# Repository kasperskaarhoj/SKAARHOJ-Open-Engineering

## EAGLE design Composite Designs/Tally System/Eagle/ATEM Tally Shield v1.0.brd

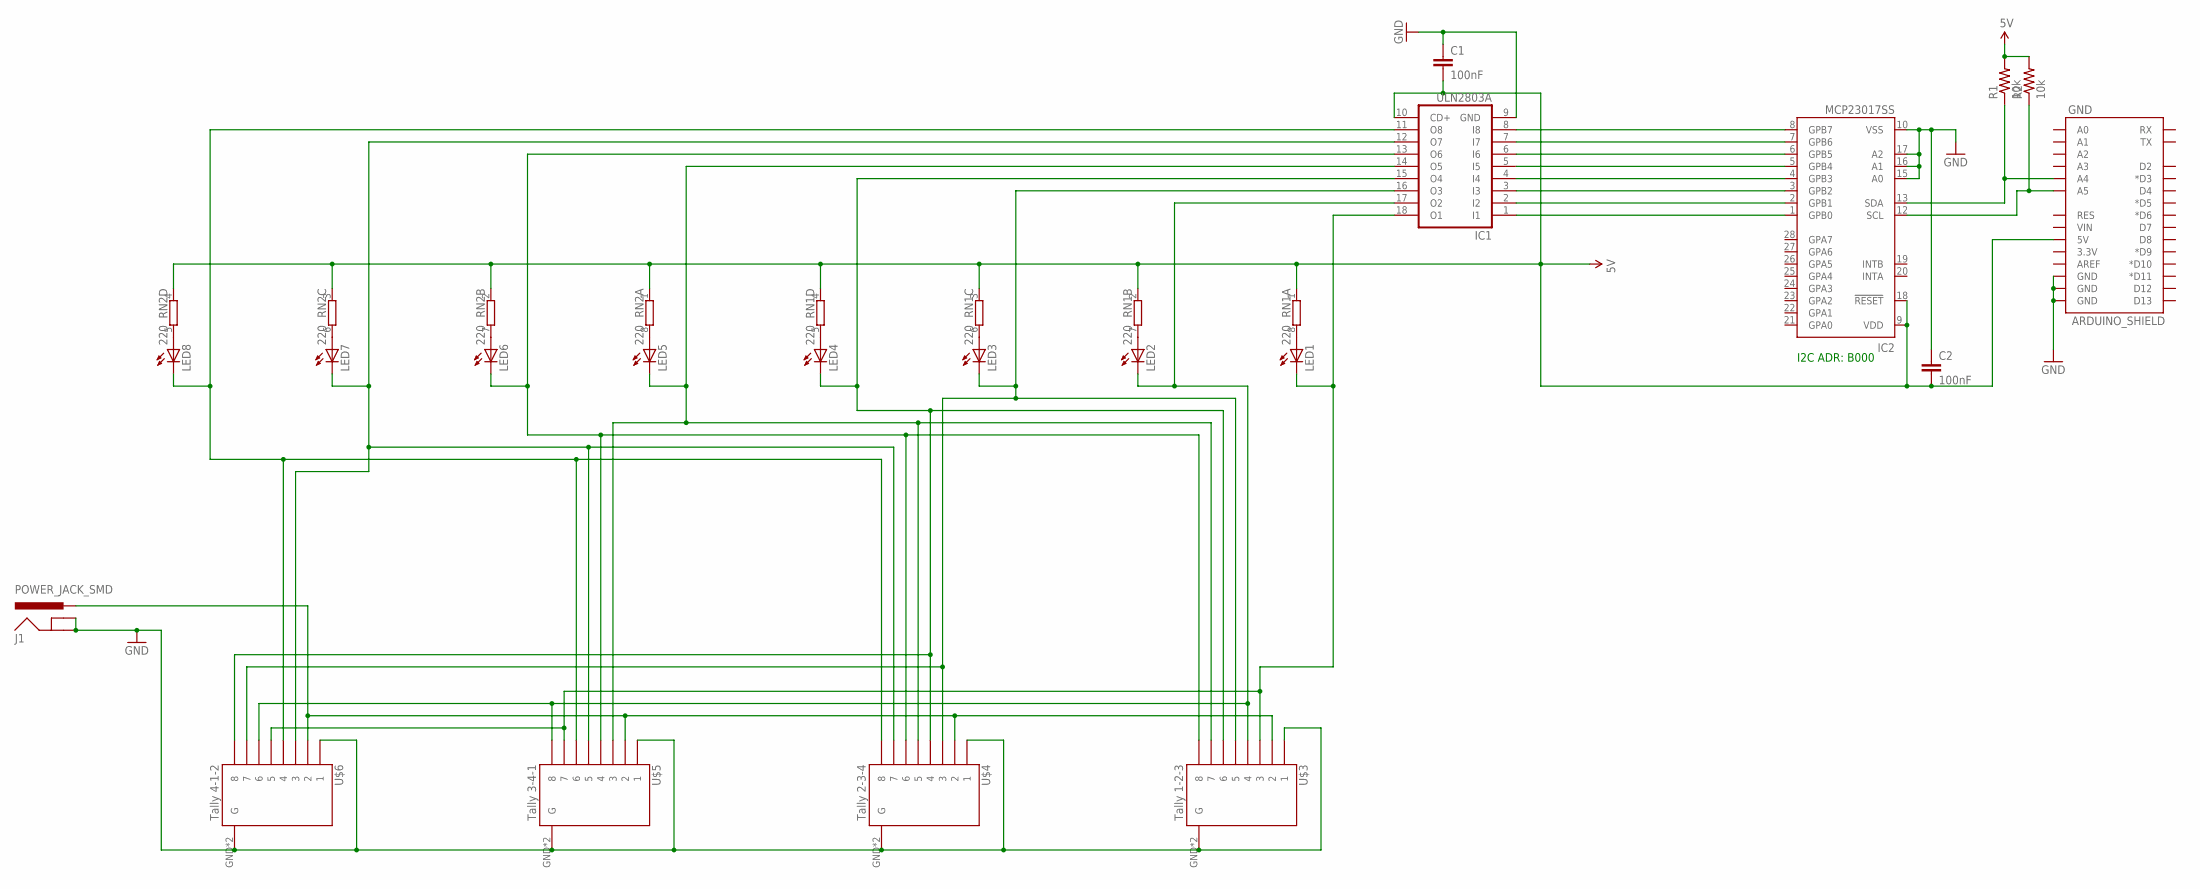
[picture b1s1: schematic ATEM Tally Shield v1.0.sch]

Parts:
C1: 100nF; 0805
C2: 100nF; 0603-CAP
GND: ARDUINO_SHIELD; ARDUINO_BOXSHIELD_NOHOLES
IC1: ULN2803A; SO18W
IC2: MCP23017SS; SSOP28
J1: POWER_JACK_SMD
LED1, LED2, LED3, LED4, LED5, LED6, LED7, LED8: LEDSML0805; SML0805
R1, R2: 10k; 0603-RES
RN1, RN2: 220; CAY16_HAND
U$3: Tally 1-2-3; RJ45-8_GND
U$4: Tally 2-3-4; RJ45-8_GND
U$5: Tally 3-4-1; RJ45-8_GND
U$6: Tally 4-1-2; RJ45-8_GND

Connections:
5V: C1.2, C2.2, GND.5V@0 (5V), IC1.10 (CD+), IC2.9 (VDD), IC2.18 (!RESET), R1.2, R2.2, RN1.1, RN1.2 (1), RN1.3 (1), RN1.4 (1), RN2.1, RN2.2 (1), RN2.3 (1), RN2.4 (1)
GND: C1.1, C2.1, GND.GND@0 (GND), GND.GND@1 (GND), GND.GND@4 (GND), IC1.9 (GND), IC2.10 (VSS), IC2.15 (A0), IC2.16 (A1), IC2.17 (A2), J1.GND, J1.SHUNT (GNDBREAK), U$3.1, U$3.GND (G), U$3.GND1 (G), U$4.1, U$4.GND (G), U$4.GND1 (G), U$5.1, U$5.GND (G), U$5.GND1 (G), U$6.1, U$6.GND (G), U$6.GND1 (G)
unnamed: IC1.18 (O1), LED1.C, U$3.3, U$5.7, U$6.5
unnamed: J1.PWR, U$3.2, U$4.2, U$5.2, U$6.2
unnamed: IC1.1 (I1), IC2.1 (GPB0)
unnamed: IC1.17 (O2), LED2.C, U$3.4, U$5.8, U$6.6
unnamed: IC1.16 (O3), LED3.C, U$3.5, U$4.3, U$6.7
unnamed: IC1.15 (O4), LED4.C, U$3.6, U$4.4, U$6.8
unnamed: IC1.14 (O5), LED5.C, U$3.7, U$4.5, U$5.3
unnamed: IC1.13 (O6), LED6.C, U$3.8, U$4.6, U$5.4
unnamed: IC1.12 (O7), LED7.C, U$4.7, U$5.5, U$6.3
unnamed: IC1.11 (O8), LED8.C, U$4.8, U$5.6, U$6.4
unnamed: IC1.2 (I2), IC2.2 (GPB1)
unnamed: IC1.3 (I3), IC2.3 (GPB2)
unnamed: IC1.4 (I4), IC2.4 (GPB3)
unnamed: IC1.5 (I5), IC2.5 (GPB4)
unnamed: IC1.6 (I6), IC2.6 (GPB5)
unnamed: IC1.7 (I7), IC2.7 (GPB6)
unnamed: IC1.8 (I8), IC2.8 (GPB7)
unnamed: LED1.A, RN1.8 (2)
unnamed: LED2.A, RN1.7 (2)
unnamed: LED3.A, RN1.6 (2)
unnamed: LED4.A, RN1.5 (2)
unnamed: LED5.A, RN2.8 (2)
unnamed: LED6.A, RN2.7 (2)
unnamed: LED7.A, RN2.6 (2)
unnamed: LED8.A, RN2.5 (2)
unnamed: GND.A5, IC2.12 (SCL), R2.1
unnamed: GND.A4, IC2.13 (SDA), R1.1

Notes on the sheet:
I2C ADR: B000

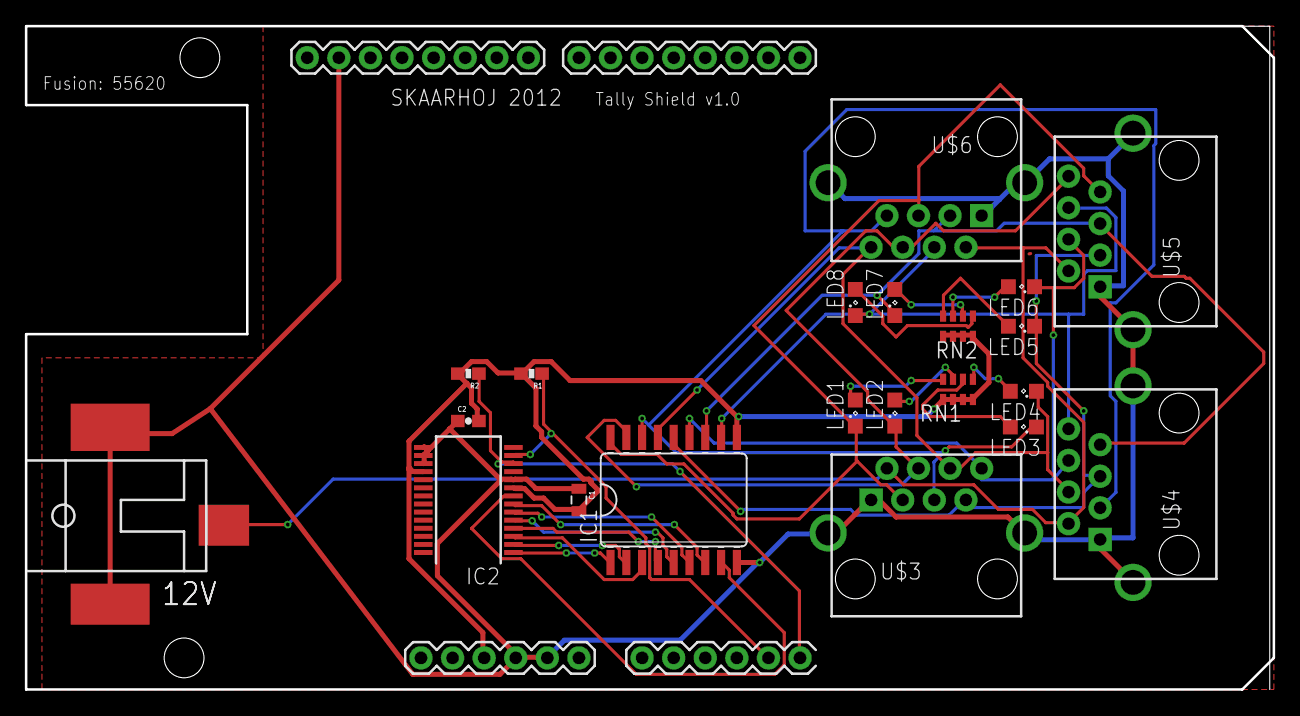
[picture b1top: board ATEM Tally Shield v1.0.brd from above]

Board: 2 copper layers, 100.3 x 53.3 mm, 22 parts (0 on the bottom side), 29 nets.

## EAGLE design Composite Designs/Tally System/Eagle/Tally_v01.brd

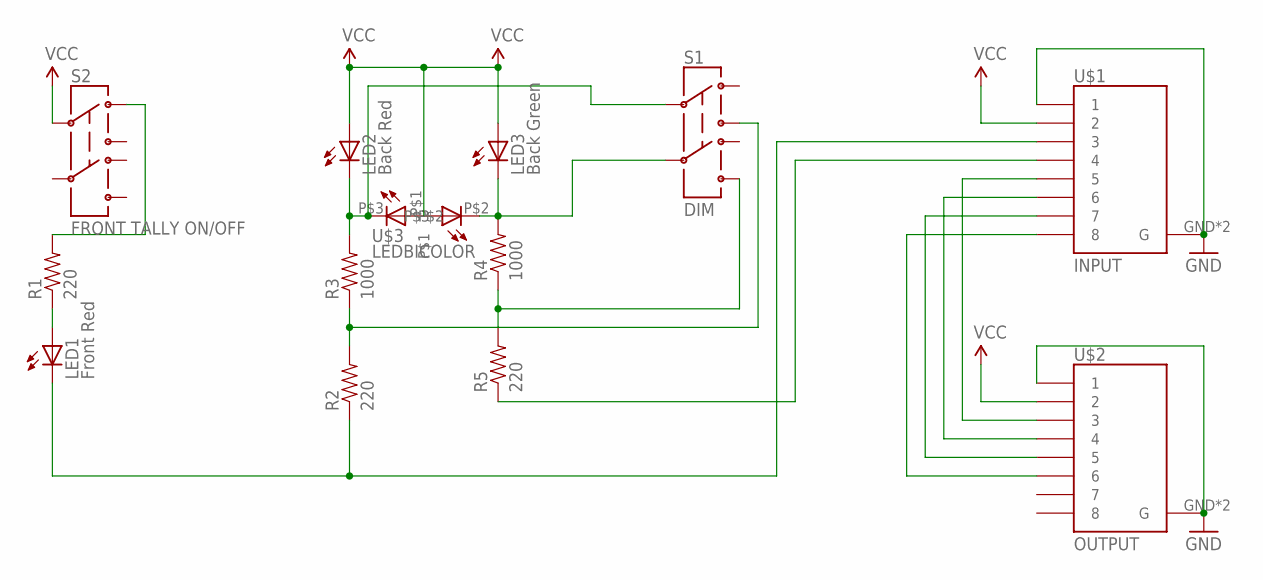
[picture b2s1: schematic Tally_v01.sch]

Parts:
LED1: Front Red; LED20
LED2: Back Red; LED20
LED3: Back Green; LED20
R1, R2, R5: 220; AXIAL-0.4
R3, R4: 1000; AXIAL-0.4
S1: DIM; TECONNECTIVITY-DPDT
S2: FRONT TALLY ON/OFF; TECONNECTIVITY-DPDT
U$1: INPUT; RJ45-8_GND
U$2: OUTPUT; RJ45-8_GND
U$3: LEDBICOLOR

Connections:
GND: U$1.1, U$1.GND (G), U$1.GND1 (G), U$2.1, U$2.GND (G), U$2.GND1 (G)
unnamed: R1.P$2 (2), S2.P$1 (1)
unnamed: LED1.P$1 (A), R1.P$1 (1)
unnamed: R2.P$2 (2), R3.P$1 (1), S1.P$3 (3)
unnamed: R4.P$1 (1), R5.P$2 (2), S1.P$6 (6)
unnamed: LED3.P$2 (C), R4.P$2 (2), S1.P$5 (5), U$3.P$2
unnamed: LED2.P$2 (C), R3.P$2 (2), S1.P$2 (2), U$3.P$3
unnamed: U$1.5, U$2.3
unnamed: U$1.6, U$2.4
unnamed: LED1.P$2 (C), R2.P$1 (1), U$1.3
unnamed: R5.P$1 (1), U$1.4
unnamed: U$1.7, U$2.5
unnamed: U$1.8, U$2.6
VCC: LED2.P$1 (A), LED3.P$1 (A), S2.P$2 (2), U$1.2, U$2.2, U$3.P$1

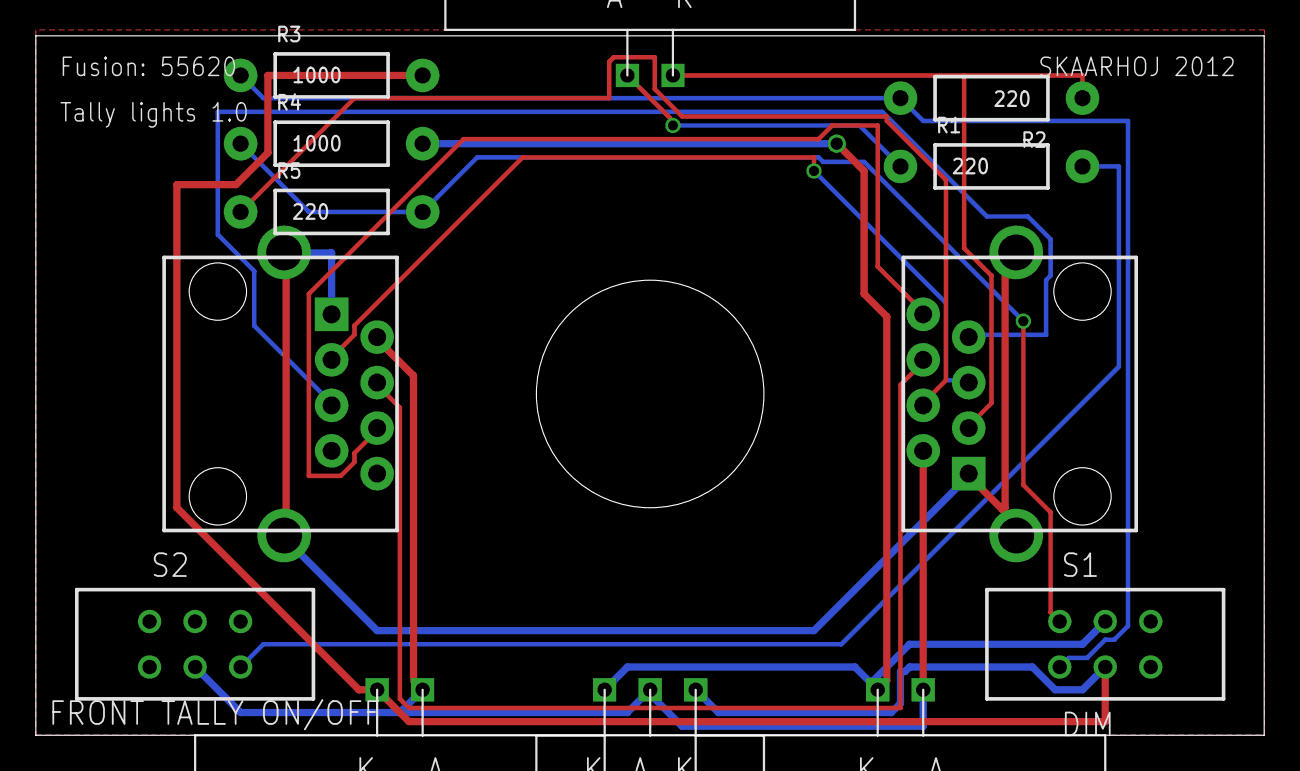
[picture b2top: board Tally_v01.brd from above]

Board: 2 copper layers, 68.6 x 39.0 mm, 13 parts (0 on the bottom side), 14 nets.

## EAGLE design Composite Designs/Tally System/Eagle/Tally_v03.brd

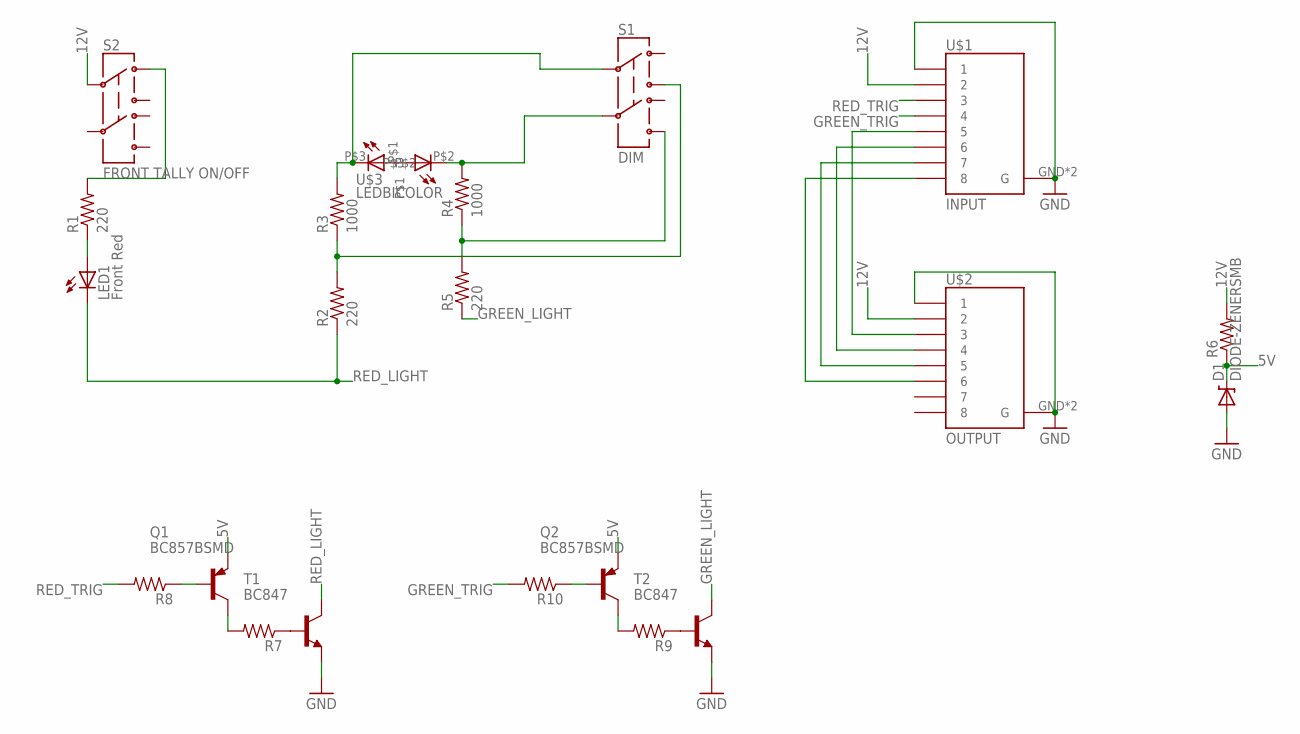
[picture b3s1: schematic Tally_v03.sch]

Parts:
D1: DIODE-ZENERSMB; SMB-DIODE
LED1: Front Red; LED20
Q1, Q2: BC857BSMD; SOT23-BEC
R1, R2, R5: 220; 0603-RES
R3, R4: 1000; 0603-RES
R6, R7, R8, R9, R10: RESISTOR0603-RES; 0603-RES
S1: DIM; TECONNECTIVITY-DPDT
S2: FRONT TALLY ON/OFF; TECONNECTIVITY-DPDT
T1, T2: BC847; SOT23
U$1: INPUT; RJ45-8_GND
U$2: OUTPUT; RJ45-8_GND
U$3: LEDBICOLOR

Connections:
5V: D1.C, Q1.E, Q2.E, R6.1
12V: R6.2, S2.P$2 (2), U$1.2, U$2.2
GND: D1.A, T1.2 (E), T2.2 (E), U$1.1, U$1.GND (G), U$1.GND1 (G), U$2.1, U$2.GND (G), U$2.GND1 (G)
GREEN_LIGHT: R5.1, T2.3 (C)
GREEN_TRIG: R10.2, U$1.4
unnamed: R1.2, S2.P$1 (1)
unnamed: LED1.P$1 (A), R1.1
unnamed: R2.2, R3.1, S1.P$3 (3)
unnamed: R4.1, R5.2, S1.P$6 (6)
unnamed: R4.2, S1.P$5 (5), U$3.P$2
unnamed: R3.2, S1.P$2 (2), U$3.P$3
unnamed: U$1.5, U$2.3
unnamed: U$1.6, U$2.4
unnamed: R7.1, T1.1 (B)
unnamed: Q1.C, R7.2
unnamed: U$1.7, U$2.5
unnamed: U$1.8, U$2.6
unnamed: R9.1, T2.1 (B)
unnamed: Q2.C, R9.2
unnamed: Q2.B, R10.1
unnamed: Q1.B, R8.1
RED_LIGHT: LED1.P$2 (C), R2.1, T1.3 (C)
RED_TRIG: R8.2, U$1.3

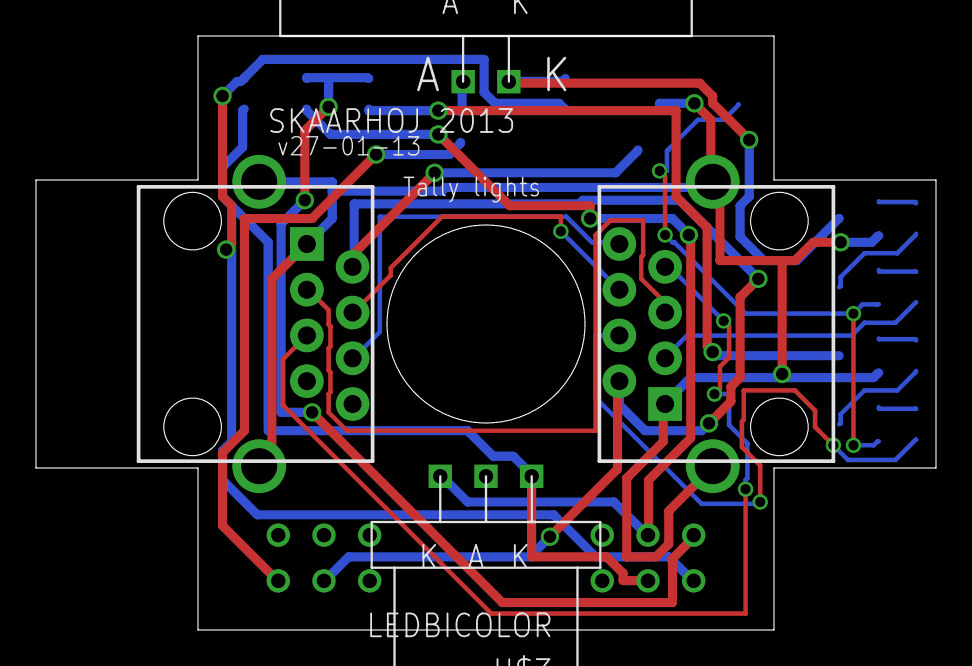
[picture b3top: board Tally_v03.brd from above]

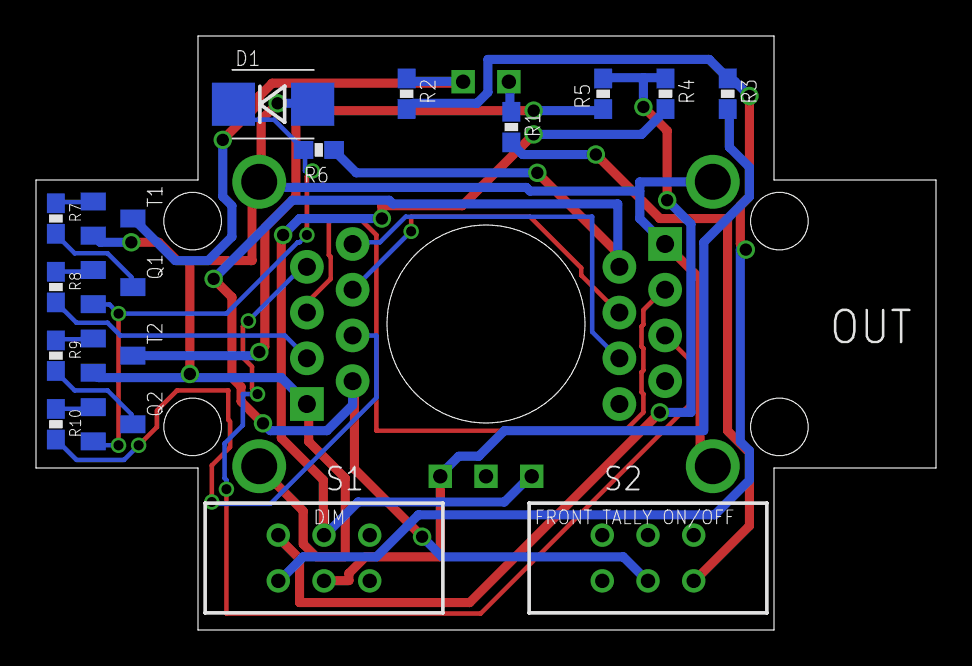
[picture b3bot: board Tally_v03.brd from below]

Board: 2 copper layers, 50.0 x 33.0 mm, 21 parts (17 on the bottom side), 23 nets.

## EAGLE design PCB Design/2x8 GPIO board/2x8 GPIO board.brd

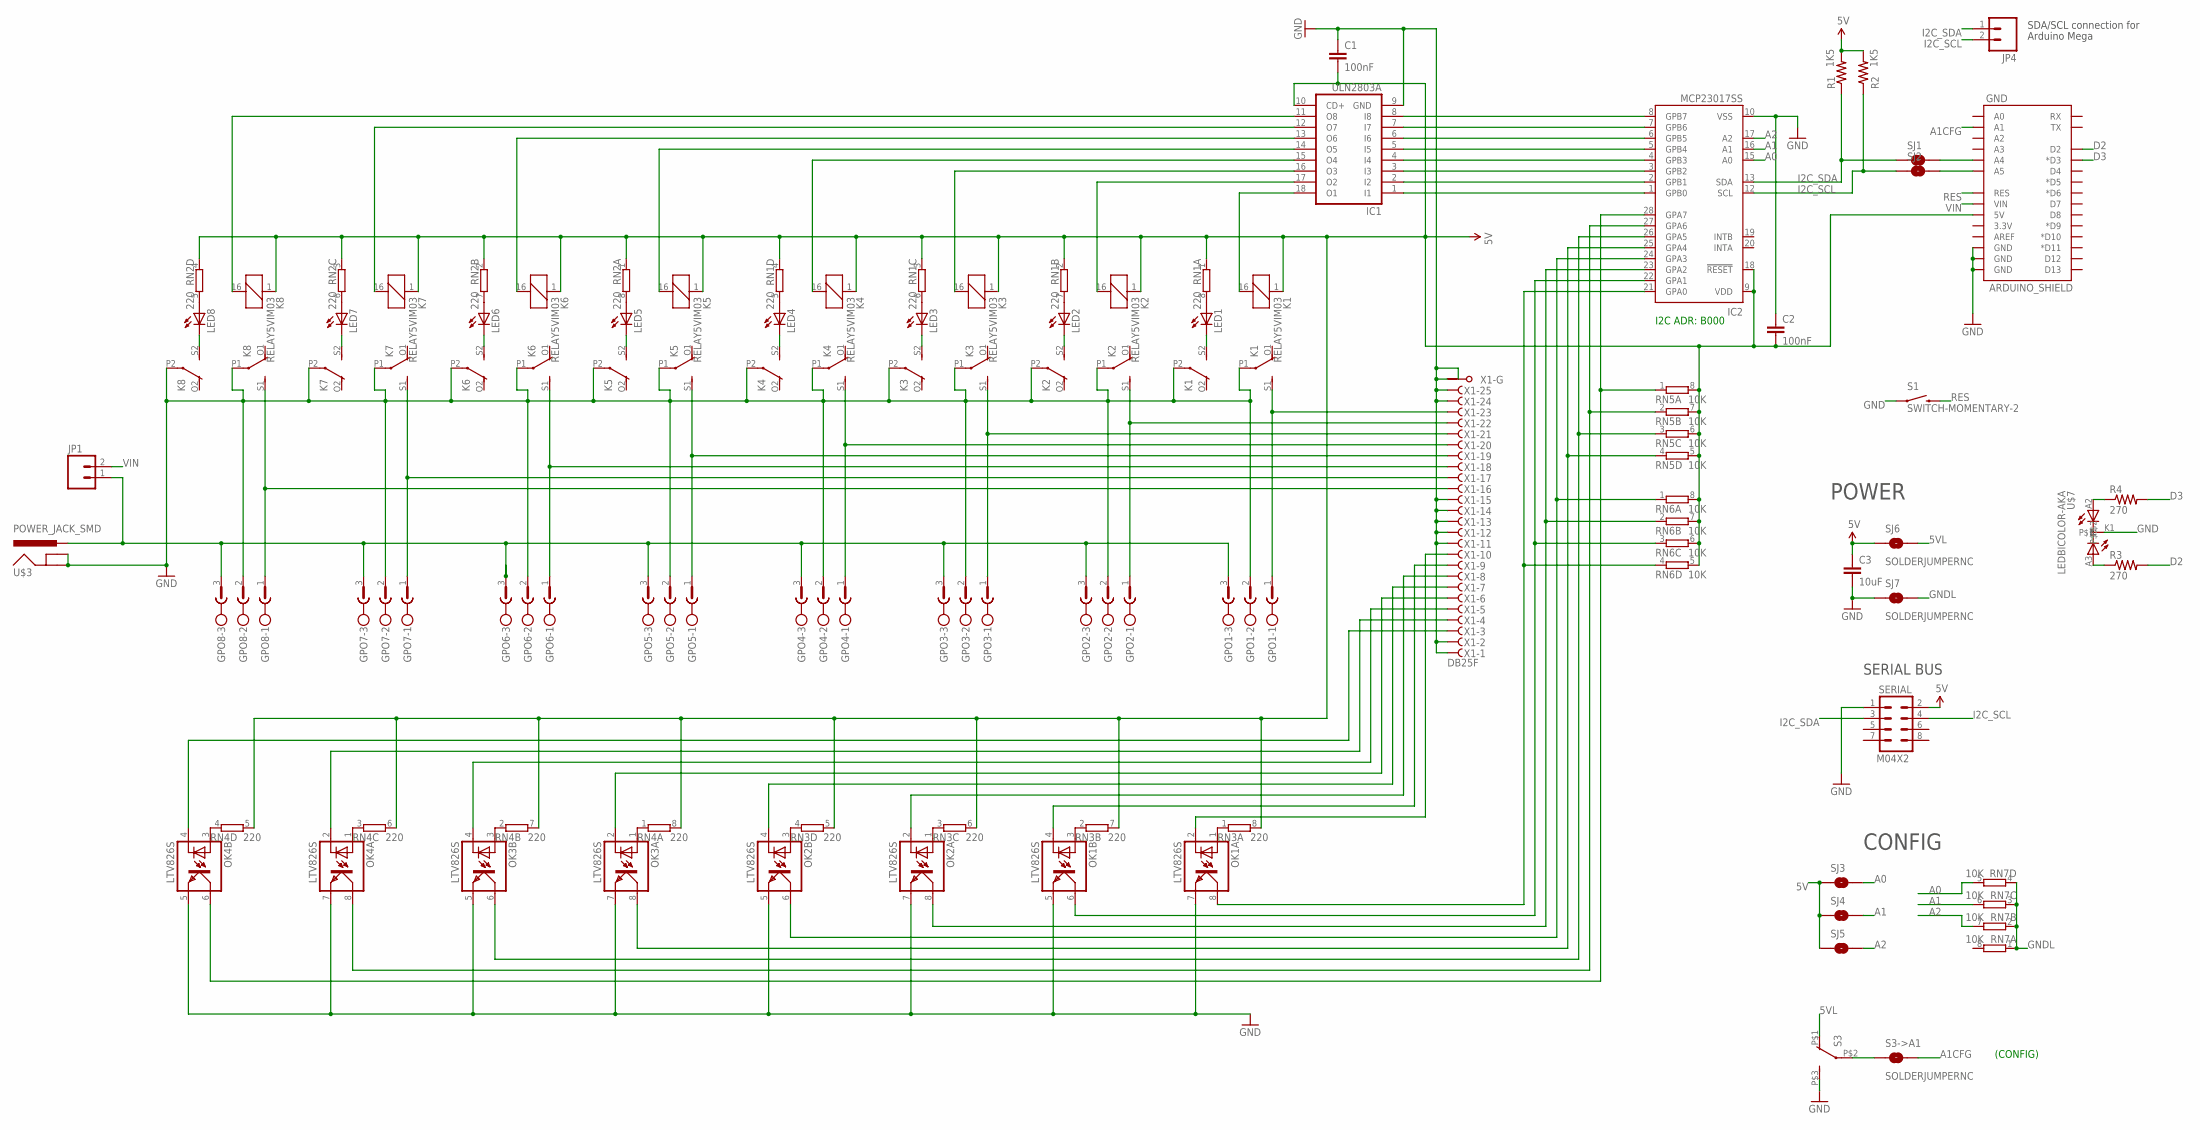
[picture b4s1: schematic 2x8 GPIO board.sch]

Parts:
C1: 100nF; 0805
C2: 100nF; 0603-CAP
C3: 10uF; 0805
GND: ARDUINO_SHIELD; ARDUINO_BOXSHIELD_NOHOLES
GPO1, GPO2, GPO3, GPO4, GPO5, GPO6, GPO7: CON1; MSTBV3
GPO8: GPO8; MSTBV3
IC1: ULN2803A; SO18W
IC2: MCP23017SS; SSOP28
JP1: M02LOCK; 1X02_LOCK
JP4: M02PTH; 1X02
K1, K2, K3, K4, K5, K6, K7, K8: RELAY5VIM03; DS2Y
LED1, LED2, LED3, LED4, LED5, LED6, LED7, LED8: LED0603; LED-0603
OK1, OK2, OK3, OK4: LTV826S; DIL8-SMD
R1, R2: 1K5; 0603-RES
R3, R4: 270; 0603-RES
RN1, RN2, RN3, RN4: 220; CAY16
RN5, RN6: 10K; CAY16
RN7: 10K; CAY16_HAND
S1: SWITCH-MOMENTARY-2; TACTILE_SWITCH_TALL
S3: CFG; TECONNECTIVITY-DPST
S3->A1: SOLDERJUMPERNC; SJ_2S
SERIAL: M04X2; 2X4
SJ1, SJ2, SJ3, SJ4, SJ5, SJ6, SJ7: SOLDERJUMPERNC; SJ_2S
U$3: POWER_JACK_SMD
U$7: LEDBICOLOR-AKA; LED5MM-BICOLOR
X1: DB25F; F25HP

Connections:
5V: C1.2, C2.2, C3.1, GND.5V@0 (5V), IC1.10 (CD+), IC2.9 (VDD), IC2.18 (!RESET), K1.1, K2.1, K3.1, K4.1, K5.1, K6.1, K7.1, K8.1, R1.2, R2.2, RN1.1, RN1.2 (1), RN1.3 (1), RN1.4 (1), RN2.1, RN2.2 (1), RN2.3 (1), RN2.4 (1), RN3.5 (2), RN3.6 (2), RN3.7 (2), RN3.8 (2), RN4.5 (2), RN4.6 (2), RN4.7 (2), RN4.8 (2), RN5.5 (2), RN5.6 (2), RN5.7 (2), RN5.8 (2), RN6.5 (2), RN6.6 (2), RN6.7 (2), RN6.8 (2), SERIAL.2, SJ3.1, SJ4.1, SJ5.1, SJ6.1
5VL: S3.P$1 (O), SJ6.2
A0: IC2.15 (A0), RN7.5 (2), SJ3.2
A1: IC2.16 (A1), RN7.6 (2), SJ4.2
A1CFG: GND.A1, S3->A1.2
A2: IC2.17 (A2), RN7.7 (2), SJ5.2
D2: GND.2 (D2), R3.2
D3: GND.3 (*D3), R4.2
GND: C1.1, C2.1, C3.2, GND.GND@0 (GND), GND.GND@1 (GND), GND.GND@4 (GND), GPO1.2, GPO2.2, GPO3.2, GPO4.2, GPO5.2, GPO6.2, GPO7.2, GPO8.2, IC1.9 (GND), IC2.10 (VSS), K1.P1, K1.P2, K2.P1, K2.P2, K3.P1, K3.P2, K4.P1, K4.P2, K5.P1, K5.P2, K6.P1, K6.P2, K7.P1, K7.P2, K8.P1, K8.P2, OK1.5 (EMIT), OK1.7 (EMIT), OK2.5 (EMIT), OK2.7 (EMIT), OK3.5 (EMIT), OK3.7 (EMIT), OK4.5 (EMIT), OK4.7 (EMIT), S1.A2 (1), S3.P$3 (S), SERIAL.1, SJ7.1, U$3.GND, U$3.SHUNT (GNDBREAK), U$7.K1, X1.1 (F), X1.2 (F), X1.11 (F), X1.12 (F), X1.13 (F), X1.14 (F), X1.15 (F), X1.24 (F), X1.25 (F), X1.G1, X1.G2
GNDL: RN7.1, RN7.2 (1), RN7.3 (1), RN7.4 (1), SJ7.2
I2C_SCL: IC2.12 (SCL), JP4.2, R2.1, SERIAL.4, SJ2.1
I2C_SDA: IC2.13 (SDA), JP4.1, R1.1, SERIAL.3, SJ1.1
unnamed: GPO1.1, K1.S1 (S), X1.23 (F)
unnamed: S3.P$2, S3->A1.1
unnamed: K1.S2 (S), LED1.C
unnamed: IC1.18 (O1), K1.16 (2)
unnamed: IC1.1 (I1), IC2.1 (GPB0)
unnamed: GPO2.1, K2.S1 (S), X1.22 (F)
unnamed: R4.1, U$7.A2
unnamed: K2.S2 (S), LED2.C
unnamed: IC1.17 (O2), K2.16 (2)
unnamed: GPO3.1, K3.S1 (S), X1.21 (F)
unnamed: R3.1, U$7.A3
unnamed: K3.S2 (S), LED3.C
unnamed: IC1.16 (O3), K3.16 (2)
unnamed: GPO4.1, K4.S1 (S), X1.20 (F)
unnamed: K4.S2 (S), LED4.C
unnamed: IC1.15 (O4), K4.16 (2)
unnamed: GPO5.1, K5.S1 (S), X1.19 (F)
unnamed: GND.A4, SJ1.2
unnamed: K5.S2 (S), LED5.C
unnamed: IC1.14 (O5), K5.16 (2)
unnamed: GPO6.1, K6.S1 (S), X1.18 (F)
unnamed: GND.A5, SJ2.2
unnamed: K6.S2 (S), LED6.C
unnamed: IC1.13 (O6), K6.16 (2)
unnamed: GPO7.1, K7.S1 (S), X1.17 (F)
unnamed: K7.S2 (S), LED7.C
unnamed: IC1.12 (O7), K7.16 (2)
unnamed: GPO8.1, K8.S1 (S), X1.16 (F)
unnamed: GPO1.3, GPO2.3, GPO3.3, GPO4.3, GPO5.3, GPO6.3, GPO7.3, GPO8.3, JP1.1, U$3.PWR
unnamed: K8.S2 (S), LED8.C
unnamed: IC1.11 (O8), K8.16 (2)
unnamed: IC1.2 (I2), IC2.2 (GPB1)
unnamed: IC1.3 (I3), IC2.3 (GPB2)
unnamed: IC1.4 (I4), IC2.4 (GPB3)
unnamed: IC1.5 (I5), IC2.5 (GPB4)
unnamed: IC1.6 (I6), IC2.6 (GPB5)
unnamed: IC1.7 (I7), IC2.7 (GPB6)
unnamed: IC1.8 (I8), IC2.8 (GPB7)
unnamed: LED1.A, RN1.8 (2)
unnamed: LED2.A, RN1.7 (2)
unnamed: LED3.A, RN1.6 (2)
unnamed: LED4.A, RN1.5 (2)
unnamed: LED5.A, RN2.8 (2)
unnamed: LED6.A, RN2.7 (2)
unnamed: LED7.A, RN2.6 (2)
unnamed: LED8.A, RN2.5 (2)
unnamed: OK1.2 (C), X1.10 (F)
unnamed: OK1.1 (A), RN3.1
unnamed: IC2.21 (GPA0), OK1.8 (COL), RN6.4 (1)
unnamed: OK1.3 (A), RN3.2 (1)
unnamed: OK2.1 (A), RN3.3 (1)
unnamed: OK2.3 (A), RN3.4 (1)
unnamed: OK3.2 (C), X1.6 (F)
unnamed: OK3.1 (A), RN4.1
unnamed: OK3.3 (A), RN4.2 (1)
unnamed: OK4.1 (A), RN4.3 (1)
unnamed: OK4.3 (A), RN4.4 (1)
unnamed: OK1.4 (C), X1.9 (F)
unnamed: OK2.2 (C), X1.8 (F)
unnamed: OK2.4 (C), X1.7 (F)
unnamed: IC2.28 (GPA7), OK4.6 (COL), RN5.1
unnamed: OK3.4 (C), X1.5 (F)
unnamed: OK4.2 (C), X1.4 (F)
unnamed: OK4.4 (C), X1.3 (F)
unnamed: IC2.22 (GPA1), OK1.6 (COL), RN6.3 (1)
unnamed: IC2.23 (GPA2), OK2.8 (COL), RN6.2 (1)
unnamed: IC2.24 (GPA3), OK2.6 (COL), RN6.1
unnamed: IC2.25 (GPA4), OK3.8 (COL), RN5.4 (1)
unnamed: IC2.26 (GPA5), OK3.6 (COL), RN5.3 (1)
unnamed: IC2.27 (GPA6), OK4.8 (COL), RN5.2 (1)
RES: GND.RESET (RES), S1.B2 (2)
VIN: GND.VIN, JP1.2

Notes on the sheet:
I2C ADR: B000
SDA/SCL connection for
Arduino Mega
SERIAL BUS
CONFIG
POWER
(CONFIG)

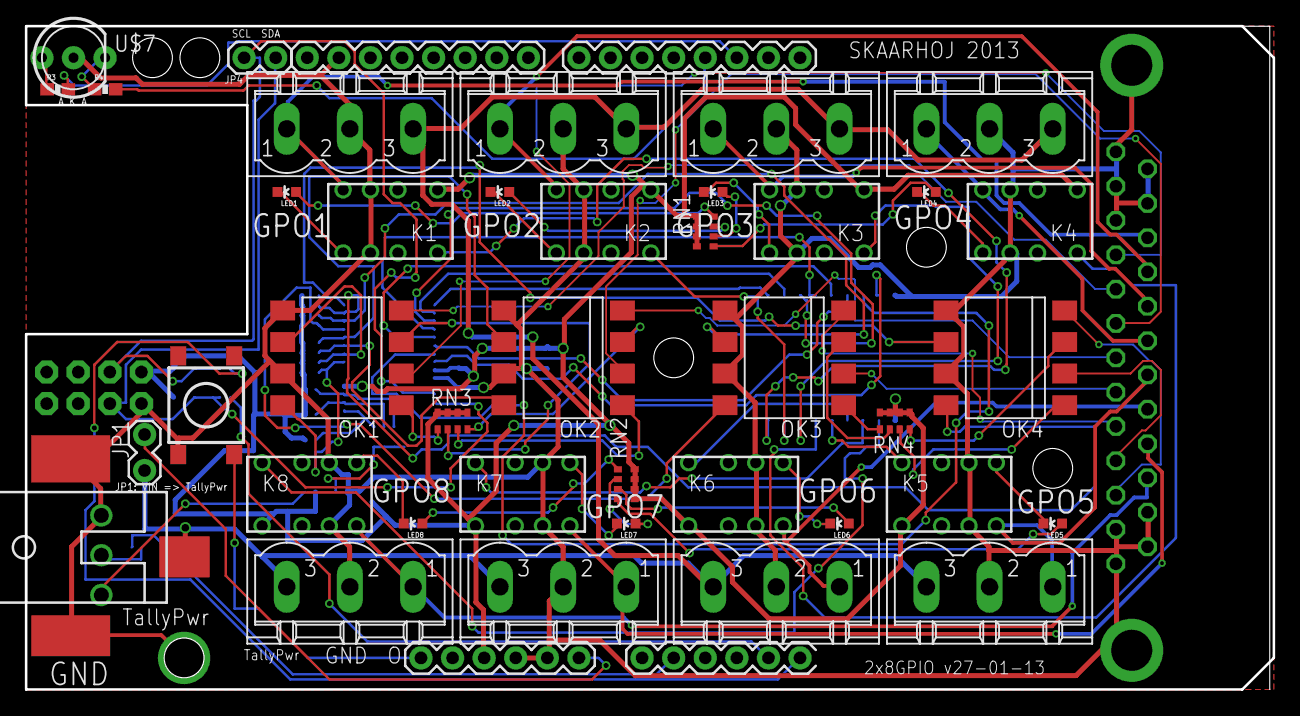
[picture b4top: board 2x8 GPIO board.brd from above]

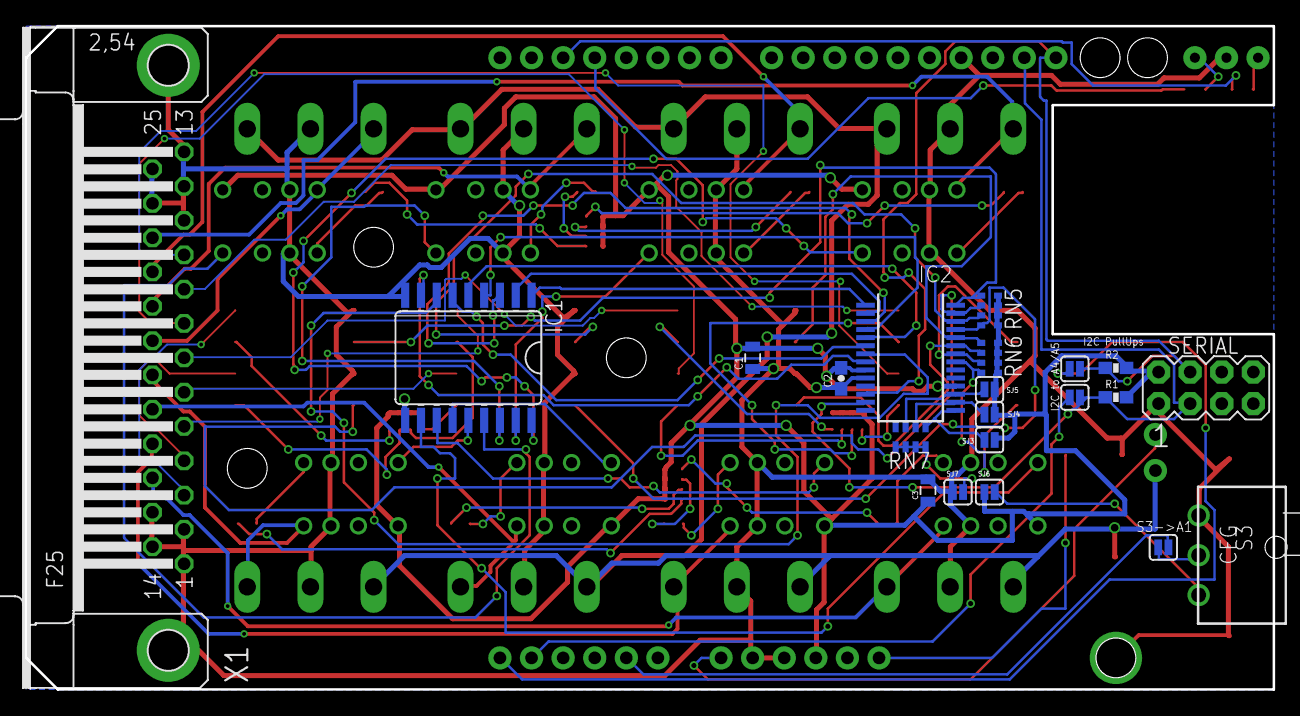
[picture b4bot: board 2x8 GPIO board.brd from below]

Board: 2 copper layers, 100.3 x 53.3 mm, 61 parts (21 on the bottom side), 84 nets.

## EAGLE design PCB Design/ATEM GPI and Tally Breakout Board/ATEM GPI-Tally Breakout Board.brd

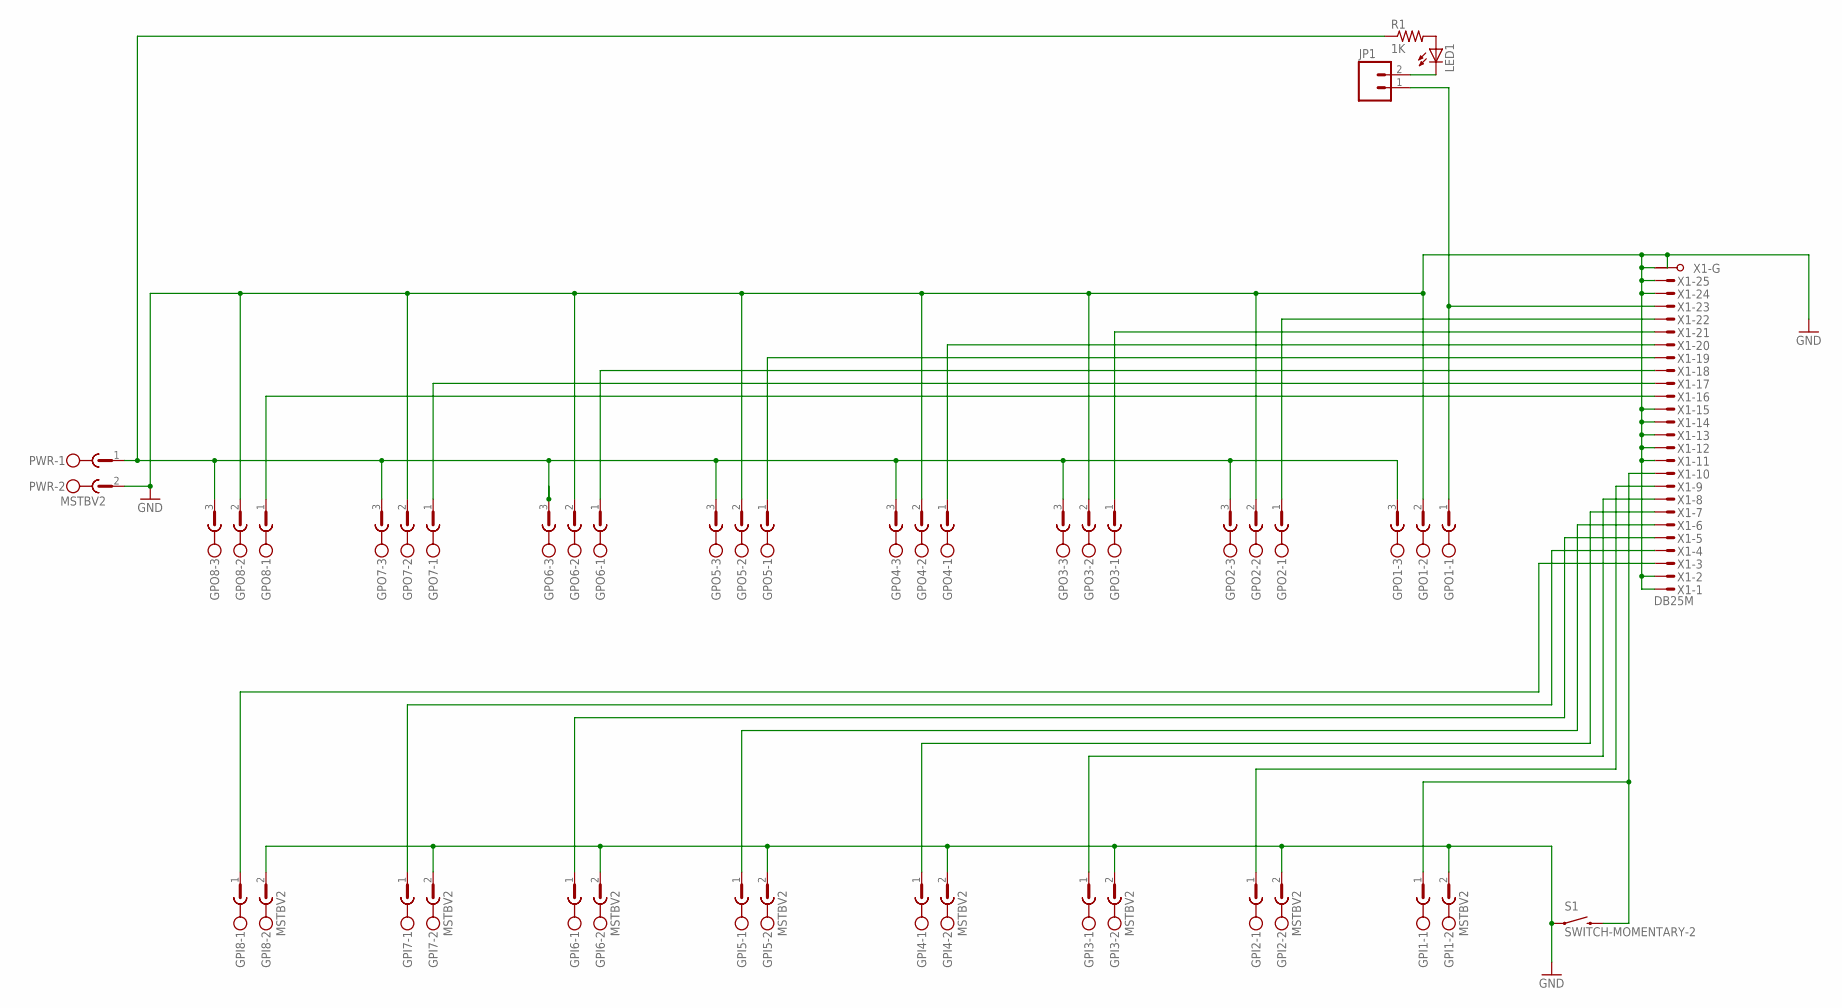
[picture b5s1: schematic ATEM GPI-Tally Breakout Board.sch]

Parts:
GPI1, GPI2, GPI3, GPI4, GPI5, GPI6, GPI7, GPI8: MSTBV2; MPN MSTBV 2,5/2-GF-5.08
GPO1, GPO2, GPO3, GPO4, GPO5, GPO6, GPO7, GPO8: CON1; MSTBV3
JP1: M02LOCK; 1X02_LOCK
LED1: LED5MM
PWR: MSTBV2
R1: 1K; AXIAL-0.4
S1: SWITCH-MOMENTARY-2; TACTILE_SWITCH_TALL
X1: DB25M; M25HP

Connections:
GND: GPI1.2, GPI2.2, GPI3.2, GPI4.2, GPI5.2, GPI6.2, GPI7.2, GPI8.2, GPO1.2, GPO2.2, GPO3.2, GPO4.2, GPO5.2, GPO6.2, GPO7.2, GPO8.2, PWR.2, S1.A2 (1), X1.1 (M), X1.2 (M), X1.11 (M), X1.12 (M), X1.13 (M), X1.14 (M), X1.15 (M), X1.24 (M), X1.25 (M), X1.G1, X1.G2
unnamed: GPO1.1, JP1.1, X1.23 (M)
unnamed: JP1.2, LED1.K (C)
unnamed: LED1.A, R1.P$2 (2)
unnamed: GPO2.1, X1.22 (M)
unnamed: GPO3.1, X1.21 (M)
unnamed: GPO4.1, X1.20 (M)
unnamed: GPO5.1, X1.19 (M)
unnamed: GPO6.1, X1.18 (M)
unnamed: GPO7.1, X1.17 (M)
unnamed: GPO8.1, X1.16 (M)
unnamed: GPI1.1, S1.B2 (2), X1.10 (M)
unnamed: GPI5.1, X1.6 (M)
unnamed: GPI2.1, X1.9 (M)
unnamed: GPI3.1, X1.8 (M)
unnamed: GPI4.1, X1.7 (M)
unnamed: GPI6.1, X1.5 (M)
unnamed: GPI7.1, X1.4 (M)
unnamed: GPI8.1, X1.3 (M)
unnamed: GPO1.3, GPO2.3, GPO3.3, GPO4.3, GPO5.3, GPO6.3, GPO7.3, GPO8.3, PWR.1, R1.P$1 (1)

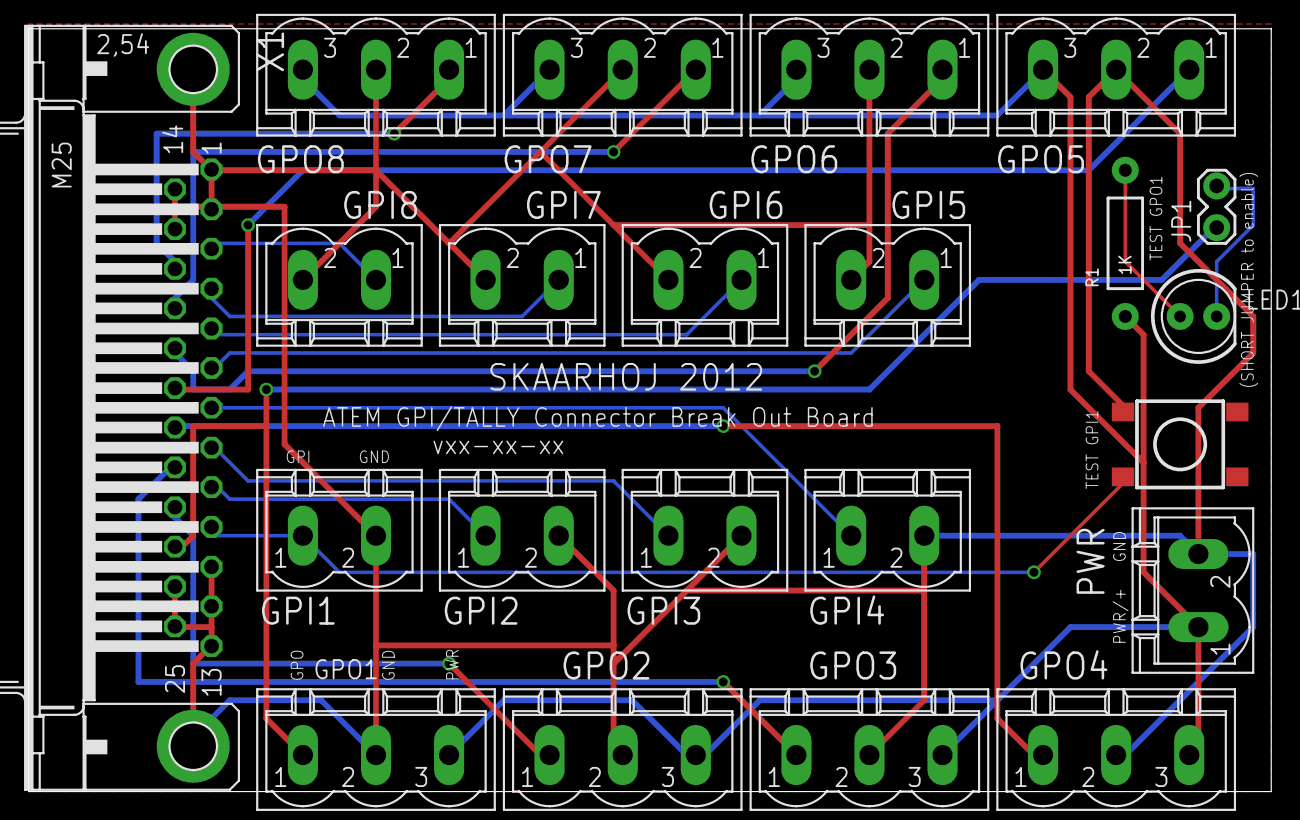
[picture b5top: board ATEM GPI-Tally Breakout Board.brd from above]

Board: 2 copper layers, 86.3 x 53.0 mm, 22 parts (0 on the bottom side), 20 nets.

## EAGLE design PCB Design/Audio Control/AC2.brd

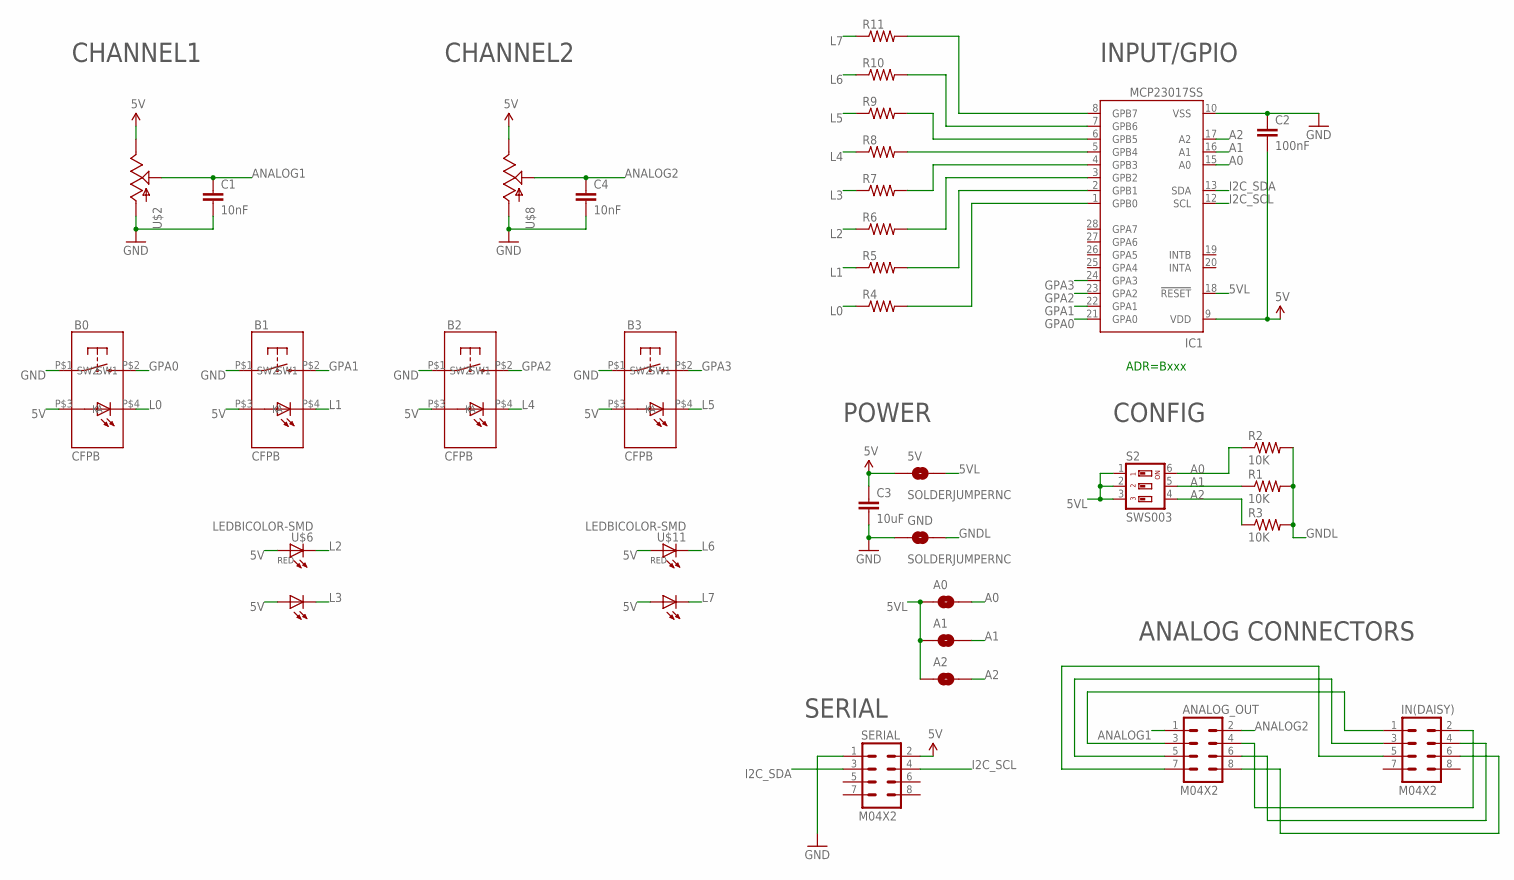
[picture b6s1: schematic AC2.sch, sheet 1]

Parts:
5V: SOLDERJUMPERNC; SJ_2S
A0, A1, A2: SOLDERJUMPERNC; SJ_2S
ANALOG_OUT: M04X2; 2X4
B0, B1, B2, B3: CFPB; CFPB-6/9MM
C1, C4: 10nF; 0603-CAP
C2: 100nF; 0603-CAP
C3: 10uF; 0805
GND: SOLDERJUMPERNC; SJ_2S
IC1: MCP23017SS; SSOP28; MPN MCP23017-E/SS
IN(DAISY): M04X2; 2X4
R1, R2, R3: 10K; 0603-RES
R4, R5, R6, R7, R8, R9, R10, R11: RESISTOR0603-RES; 0603-RES
S2: SWS003; SMS-003
SERIAL: M04X2; 2X4
U$2, U$8: POT; ALPS_POT
U$6, U$11: LEDBICOLOR-SMD

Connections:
5V: 5V.1, B0.P$3 (A), B1.P$3 (A), B2.P$3 (A), B3.P$3 (A), C2.2, C3.1, IC1.9 (VDD), SERIAL.2, U$2.P$1 (E), U$6.P$1 (A), U$6.P$3 (A1), U$8.P$1 (E), U$11.P$1 (A), U$11.P$3 (A1)
5VL: 5V.2, A0.1, A1.1, A2.1, IC1.18 (!RESET), S2.1, S2.2, S2.3
A0: A0.2, IC1.15 (A0), R2.1, S2.6
A1: A1.2, IC1.16 (A1), R1.1, S2.5
A2: A2.2, IC1.17 (A2), R3.1, S2.4
ANALOG1: ANALOG_OUT.1, C1.1, U$2.P$2 (S)
ANALOG2: ANALOG_OUT.2, C4.1, U$8.P$2 (S)
GND: B0.P$1 (SW1), B1.P$1 (SW1), B2.P$1 (SW1), B3.P$1 (SW1), C1.2, C2.1, C3.2, C4.2, GND.1, IC1.10 (VSS), SERIAL.1, U$2.P$3 (A), U$8.P$3 (A)
GNDL: GND.2, R1.2, R2.2, R3.2
GPA0: B0.P$2 (SW2), IC1.21 (GPA0)
GPA1: B1.P$2 (SW2), IC1.22 (GPA1)
GPA2: B2.P$2 (SW2), IC1.23 (GPA2)
GPA3: B3.P$2 (SW2), IC1.24 (GPA3)
I2C_SCL: IC1.12 (SCL), SERIAL.4
I2C_SDA: IC1.13 (SDA), SERIAL.3
L0: B0.P$4 (K), R4.1
L1: B1.P$4 (K), R5.1
L2: R6.1, U$6.P$2 (C)
L3: R7.1, U$6.P$4 (C1)
L4: B2.P$4 (K), R8.1
L5: B3.P$4 (K), R9.1
L6: R10.1, U$11.P$2 (C)
L7: R11.1, U$11.P$4 (C1)
unnamed: IC1.4 (GPB3), R7.2
unnamed: IC1.5 (GPB4), R8.2
unnamed: IC1.6 (GPB5), R9.2
unnamed: IC1.7 (GPB6), R10.2
unnamed: IC1.8 (GPB7), R11.2
unnamed: IC1.3 (GPB2), R6.2
unnamed: IC1.2 (GPB1), R5.2
unnamed: IC1.1 (GPB0), R4.2
unnamed: ANALOG_OUT.3, IN(DAISY).1
unnamed: ANALOG_OUT.5, IN(DAISY).3
unnamed: ANALOG_OUT.7, IN(DAISY).5
unnamed: ANALOG_OUT.4, IN(DAISY).2
unnamed: ANALOG_OUT.6, IN(DAISY).4
unnamed: ANALOG_OUT.8, IN(DAISY).6

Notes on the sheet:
SERIAL
ADR=Bxxx
INPUT/GPIO
POWER
CONFIG
ANALOG CONNECTORS
CHANNEL1
CHANNEL2

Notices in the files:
parts and their libraries:
SparkFun: Licensing: CC v3.0 Share-Alike You are welcome to use this library for commercial purposes.
